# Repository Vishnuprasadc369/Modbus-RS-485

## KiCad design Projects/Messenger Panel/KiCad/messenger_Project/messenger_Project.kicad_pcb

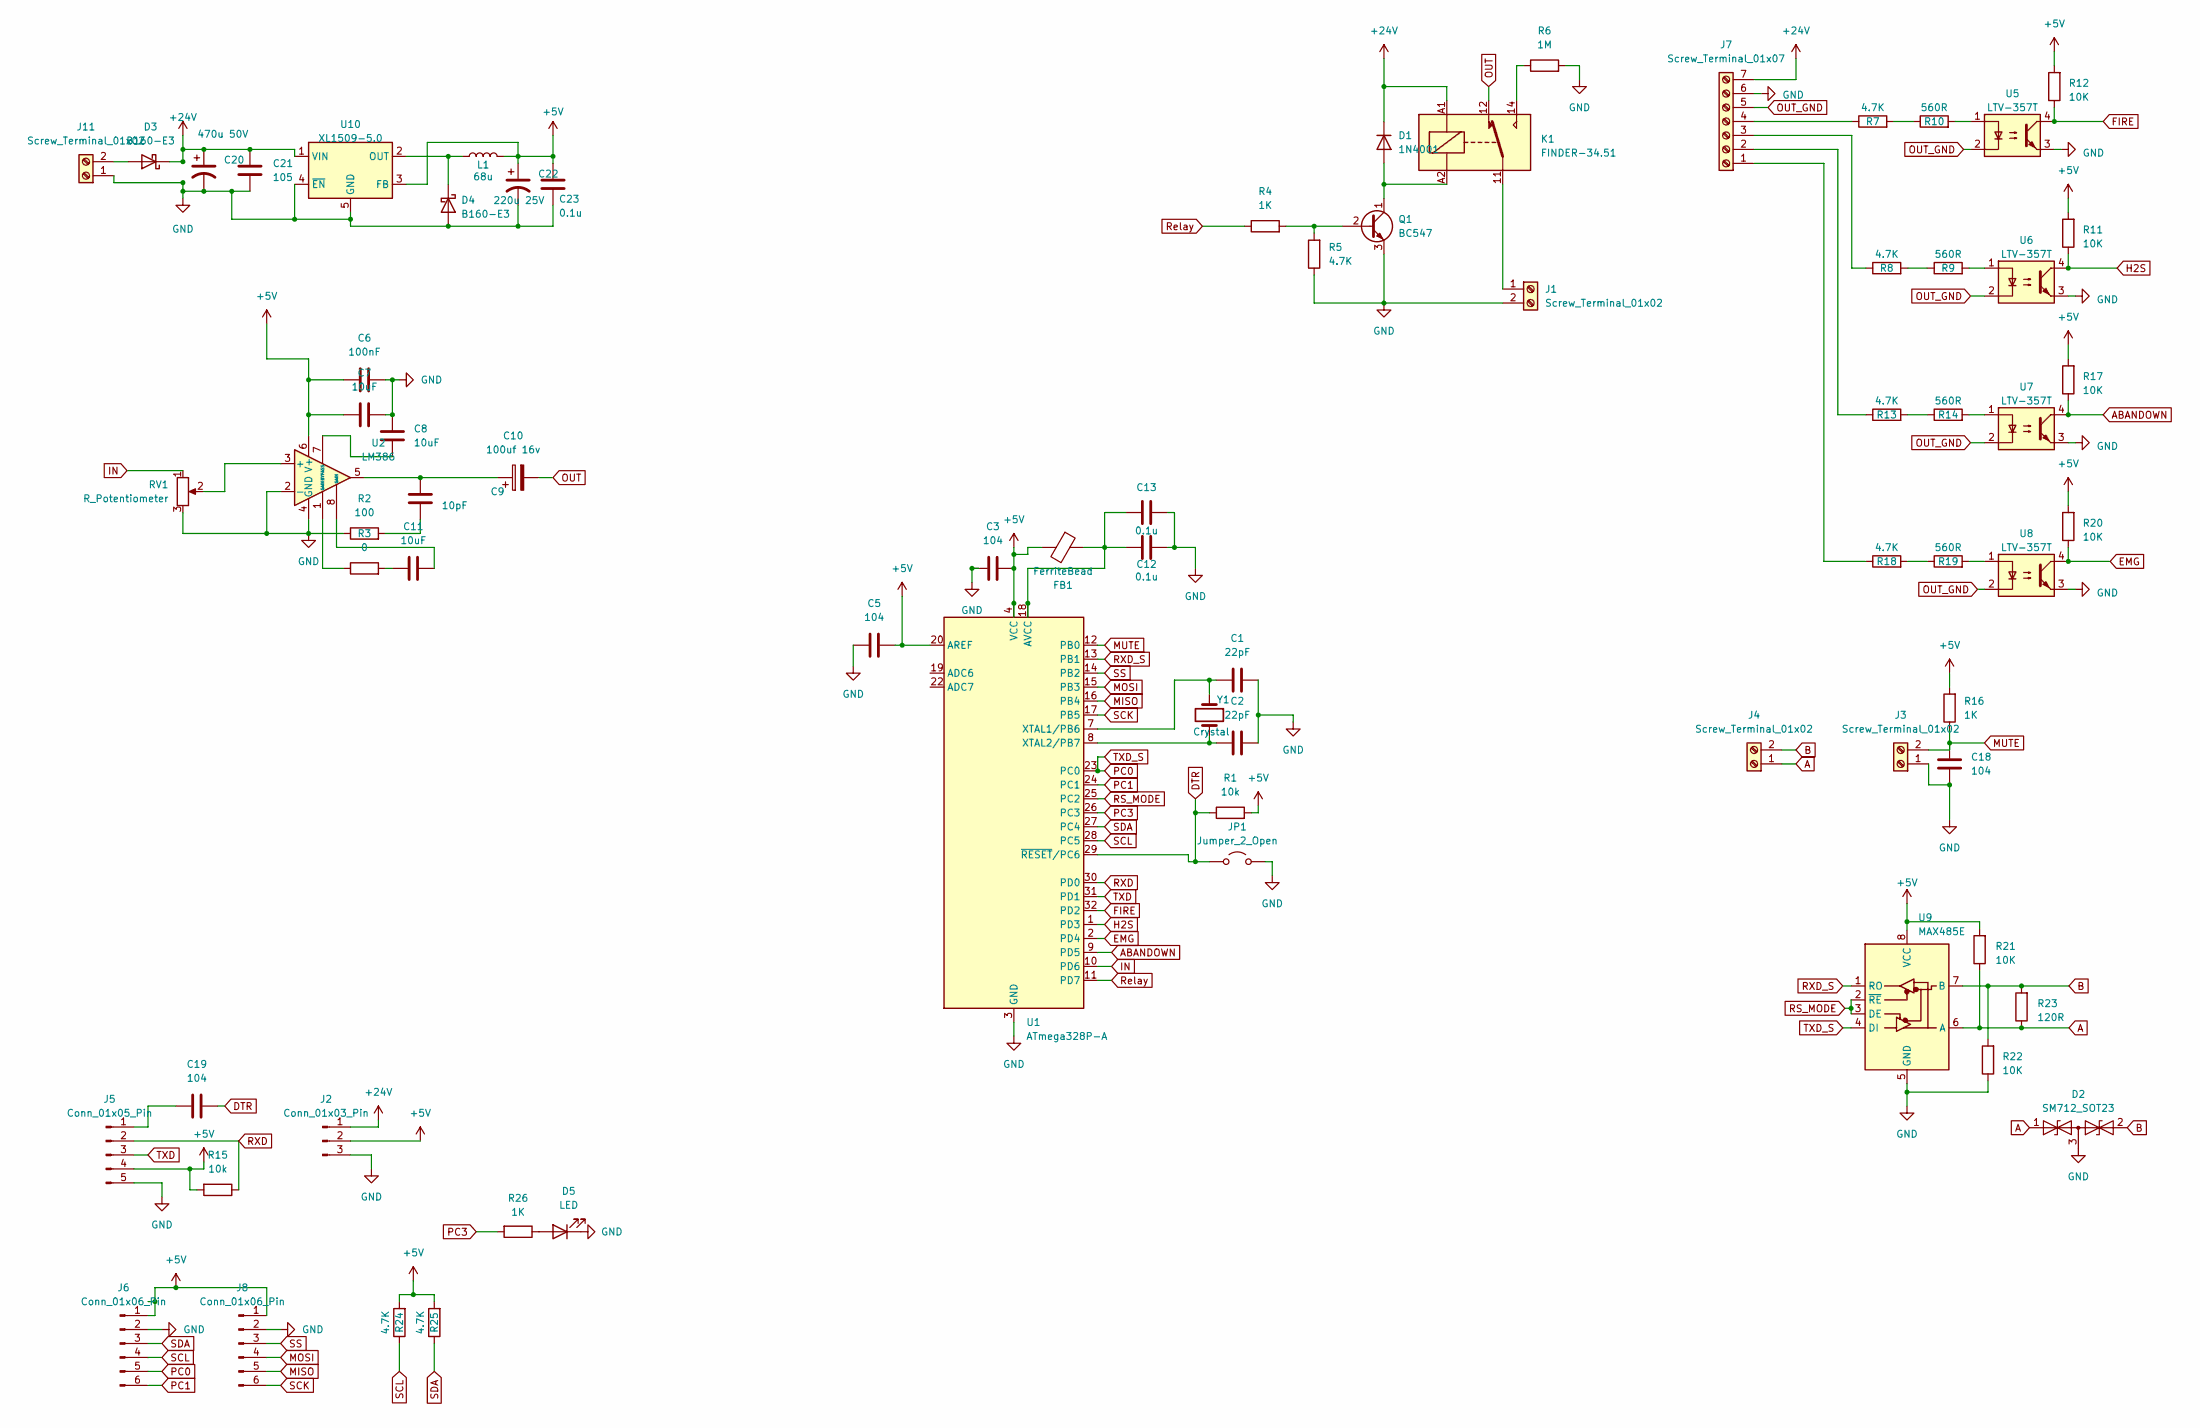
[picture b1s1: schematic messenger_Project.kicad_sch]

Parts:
C1, C2: 22pF; C_0805_2012Metric
C3, C5, C18, C19: 104; C_0805_2012Metric
C6: 100nF; C_0805_2012Metric
C7, C8, C11: 10uF; C_0805_2012Metric
C9: 10pF; C_0805_2012Metric
C10: 100uf 16v; CP_Radial_D5.0mm_P2.50mm
C12, C13, C23: 0.1u; C_0805_2012Metric
C20: 470u 50V; CP_Radial_D10.0mm_P5.00mm
C21: 105; C_Disc_D5.1mm_W3.2mm_P5.00mm
C22: 220u 25V; CP_Radial_D8.0mm_P5.00mm
D1: 1N4001; D_DO-41_SOD81_P10.16mm_Horizontal
D2: SM712_SOT23; SOT-23
D3, D4: B160-E3; D_SMA
D5: LED; LED_D3.0mm
FB1: FerriteBead; L_0805_2012Metric
J1, J3, J4, J11: Screw_Terminal_01x02; TerminalBlock_Phoenix_MKDS-1,5-2_1x02_P5.00mm_Horizontal
J2: Conn_01x03_Pin; PinHeader_1x03_P2.54mm_Vertical
J5: Conn_01x05_Pin; PinHeader_1x05_P2.54mm_Vertical
J6, J8: Conn_01x06_Pin; PinHeader_1x06_P2.54mm_Vertical
J7: Screw_Terminal_01x07; TerminalBlock_Phoenix_MKDS-1,5-7-5.08_1x07_P5.08mm_Horizont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
JP1: Jumper_2_Open; SolderJumper-2_P1.3mm_Open_Pad1.0x1.5mm
K1: FINDER-34.51; Relay_SPDT_Finder_34.51_Vertical
L1: 68u; L_Sunlord_SWPA6045S
Q1: BC547; TO-92_Inline
R1, R15: 10k; R_0805_2012Metric
R2: 100; R_0805_2012Metric
R3: 0; R_0805_2012Metric
R4, R16, R26: 1K; R_0805_2012Metric
R5, R7, R8, R13, R18, R24, R25: 4.7K; R_0805_2012Metric
R6: 1M; R_0805_2012Metric
R9, R10, R14, R19: 560R; R_0805_2012Metric
R11, R12, R17, R20, R21, R22: 10K; R_0805_2012Metric
R23: 120R; R_0805_2012Metric
RV1: R_Potentiometer; Potentiometer_Runtron_RM-065_Vertical
U1: ATmega328P-A; TQFP-32_7x7mm_P0.8mm
U2: LM386; SOIC-8_3.9x4.9mm_P1.27mm
U5, U6, U7, U8: LTV-357T; SO-4_4.4x3.6mm_P2.54mm
U9: MAX485E; SOIC-8_3.9x4.9mm_P1.27mm
U10: XL1509-5.0; SOIC-8_3.9x4.9mm_P1.27mm
Y1: Crystal; Crystal_HC49-U_Vertical

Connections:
+5V: C3.2, C5.2, C6.1, C7.1, C22.1, C23.1, FB1.2, J2.2, J5.4, J6.1, J8.1, L1.2, R1.2, R11.2, R12.2, R15.2, R16.2, R17.2, R20.2, R21.2, R24.2, R25.2, U1.4 (VCC), U1.6 (VCC), U1.20 (AREF), U2.6 (V+), U9.8 (VCC), U10.3 (FB)
+24V: C20.1, C21.1, D1.1 (K), D3.1 (K), J2.1, J7.7, K1.A1, U10.1 (VIN)
A: D2.1 (A1), J4.1, R21.1, R23.1, U9.6 (A)
ABANDOWN: R17.1, U1.9 (PD5), U7.4
B: D2.2 (A2), J4.2, R22.2, R23.2, U9.7 (B)
DTR: C19.2, JP1.1 (A), R1.1, U1.29 (~RESET/PC6)
EMG: R20.1, U1.2 (PD4), U8.4
FIRE: R12.1, U1.32 (PD2), U5.4
GND: C1.2, C2.2, C3.1, C5.1, C6.2, C7.2, C8.2, C12.2, C13.2, C18.1, C20.2, C21.2, C22.2, C23.2, D2.3 (common), D4.2 (A), D5.1 (K), J1.2, J2.3, J3.1, J5.5, J6.2, J7.6, J8.2, J11.1, JP1.2 (B), Q1.3 (E), R2.1, R5.1, R6.2, R22.1, RV1.3, U1.3 (GND), U1.5 (GND), U1.21 (GND), U2.2 (-), U2.4 (GND), U5.3, U6.3, U7.3, U8.3, U9.5 (GND), U10.4 (~EN), U10.5 (GND), U10.6 (GND), U10.7 (GND), U10.8 (GND)
H2S: R11.1, U1.1 (PD3), U6.4
IN: RV1.1, U1.10 (PD6)
MISO: J8.5, U1.16 (PB4)
MOSI: J8.4, U1.15 (PB3)
MUTE: C18.2, J3.2, R16.1, U1.12 (PB0)
unnamed: C9.1, R2.2
unnamed: C9.2, C10.1, U2.5
unnamed: C11.1, U2.8 (GAIN)
unnamed: C11.2, R3.2
unnamed: D1.2 (A), K1.A2, Q1.1 (C)
unnamed: D3.2 (A), J11.2
unnamed: D4.1 (K), L1.1, U10.2 (OUT)
unnamed: D5.2 (A), R26.1
unnamed: J1.1, K1.11
unnamed: C19.1, J5.1
unnamed: J7.1, R18.1
unnamed: J7.2, R13.1
unnamed: J7.3, R8.1
unnamed: J7.4, R7.1
unnamed: K1.14, R6.1
unnamed: Q1.2 (B), R4.2, R5.2
unnamed: R3.1, U2.1 (GAIN)
unnamed: R8.2, R9.1
unnamed: R9.2, U6.1
unnamed: R7.2, R10.1
unnamed: R10.2, U5.1
unnamed: R13.2, R14.1
unnamed: R14.2, U7.1
unnamed: R18.2, R19.1
unnamed: R19.2, U8.1
unnamed: C12.1, C13.1, FB1.1, U1.18 (AVCC)
unnamed: C1.1, U1.7 (XTAL1/PB6), Y1.1
unnamed: C2.1, U1.8 (XTAL2/PB7), Y1.2
unnamed: RV1.2, U2.3 (+)
unnamed: C8.1, U2.7 (BYPASS)
OUT: C10.2, K1.12
OUT_GND: J7.5, U5.2, U6.2, U7.2, U8.2
PC0: J6.5, U1.23 (PC0), U9.4 (DI)
PC1: J6.6, U1.24 (PC1)
PC3: R26.2, U1.26 (PC3)
RS_MODE: U1.25 (PC2), U9.2 (~RE), U9.3 (DE)
RXD: J5.2, R15.1, U1.30 (PD0)
RXD_S: U1.13 (PB1), U9.1 (RO)
Relay: R4.1, U1.11 (PD7)
SCK: J8.6, U1.17 (PB5)
SCL: J6.4, R24.1, U1.28 (PC5)
SDA: J6.3, R25.1, U1.27 (PC4)
SS: J8.3, U1.14 (PB2)
TXD: J5.3, U1.31 (PD1)

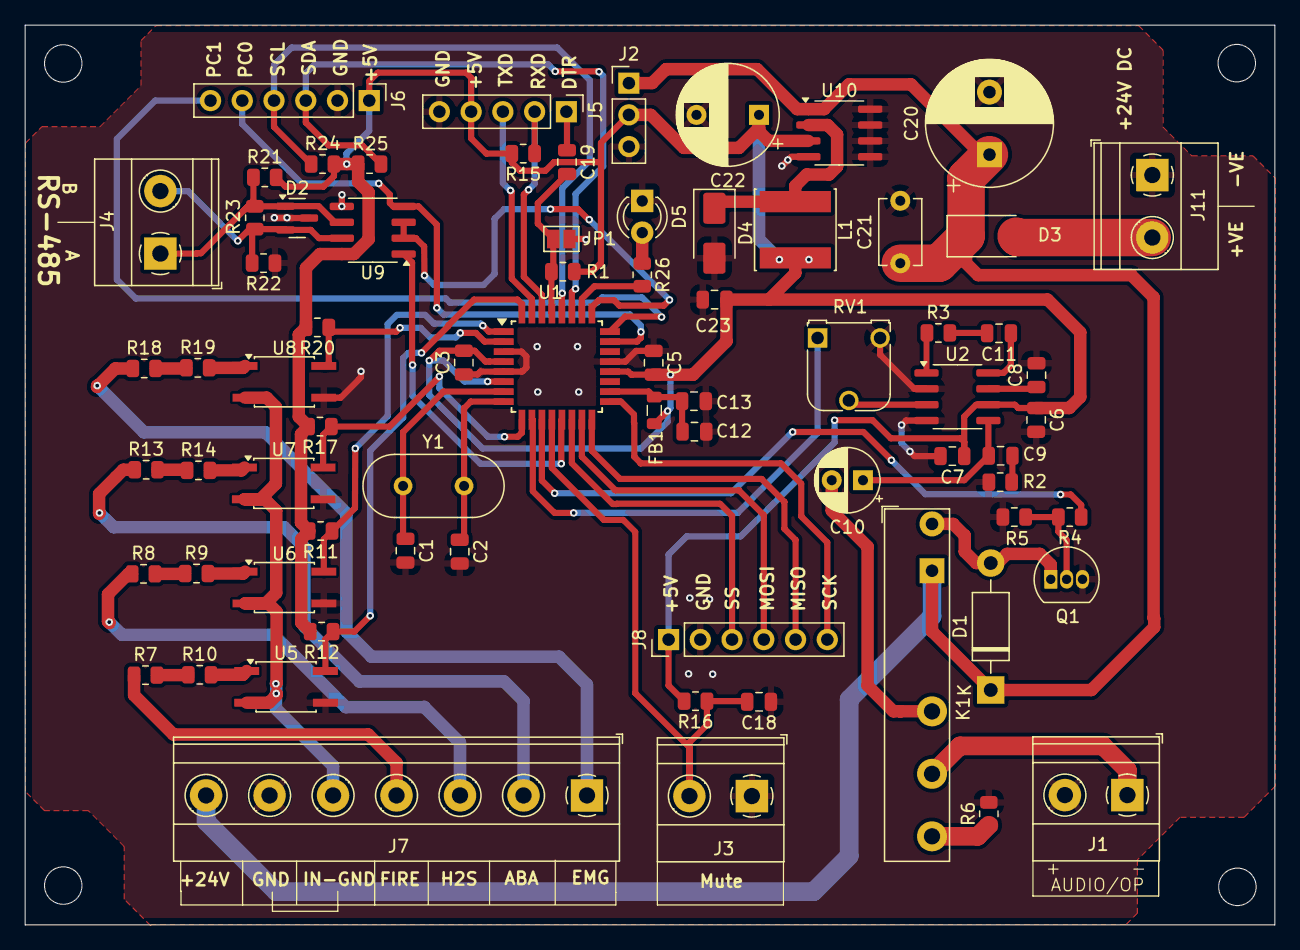
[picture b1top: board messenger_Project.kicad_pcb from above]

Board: 2 copper layers, 100.0 x 72.0 mm, 73 parts (0 on the bottom side), 58 nets.
